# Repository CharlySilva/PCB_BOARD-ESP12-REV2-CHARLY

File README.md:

# PCB_BOARD-ESP12-REV2-CHARLY
# PCB in fabrication fase

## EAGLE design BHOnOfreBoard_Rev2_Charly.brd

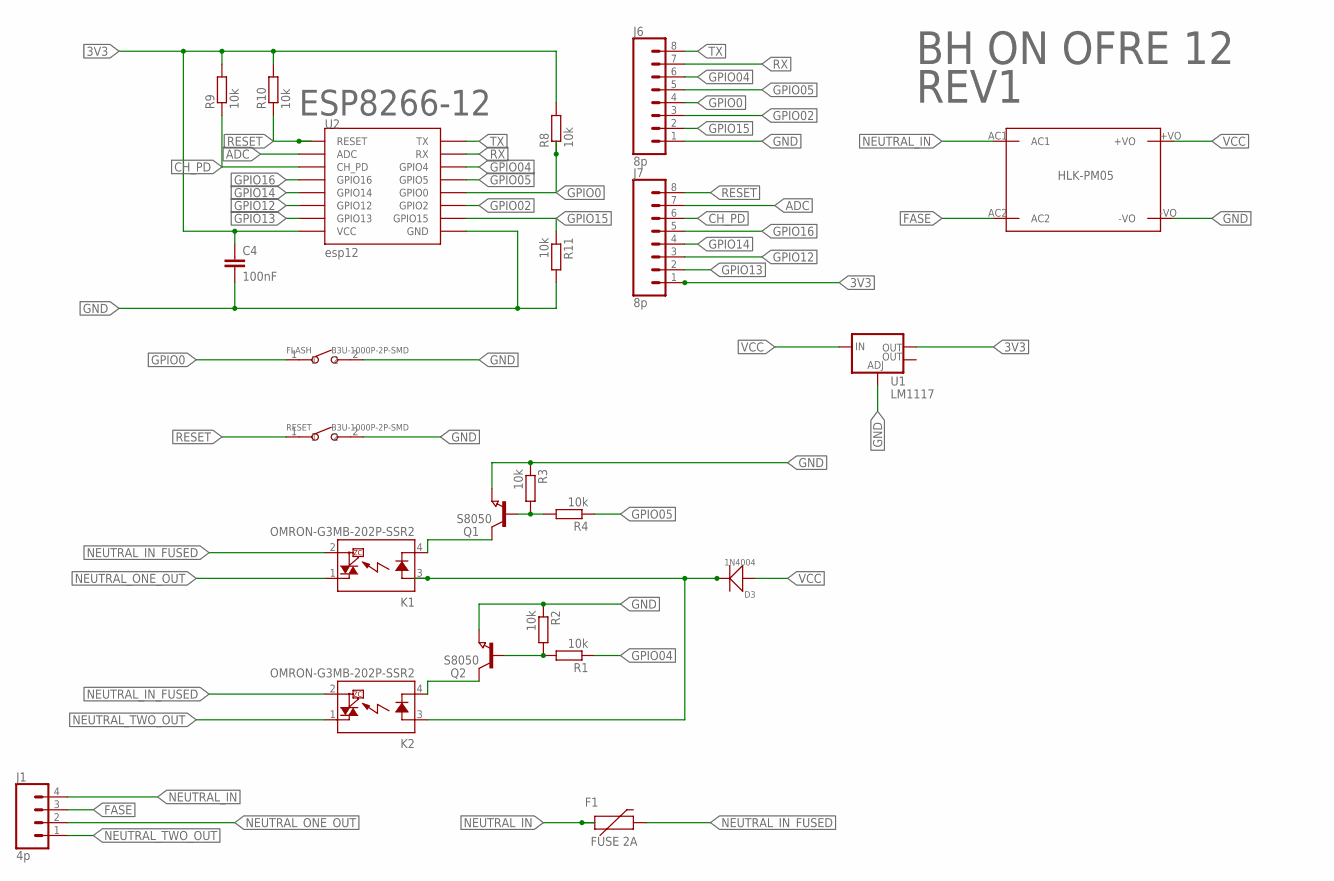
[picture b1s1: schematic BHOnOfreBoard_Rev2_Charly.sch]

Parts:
C4: 100nF; 0603
D3: 1N4004; DO-214AC
F1: FUSE 2A; PTH
FLASH: B3U-1000P-2P-SMD; SW2-2.6-3.0X2.5X1.2+0.4MM
J1: 4p; SCREWTERMINAL-3.5MM-4
J6, J7: 8p; 1X08
K1, K2: OMRON-G3MB-202P-SSR2; OMRON-G3MB-202P-SSR
Q1, Q2: S8050; SOT23
R1, R2, R3, R4, R8, R9, R10, R11: 10k; R0603
RESET: B3U-1000P-2P-SMD; SW2-2.6-3.0X2.5X1.2+0.4MM
U1: LM1117; SOT223
U2: esp12; ESP12-SMD
U$2: HLK-PM03

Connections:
3V3: C4.1, J7.1, R8.2, R9.2, R10.2, U1.2 (OUT), U2.VCC
ADC: J7.7, U2.ADC
CH_PD: J7.6, R9.1, U2.CH_PD
FASE: J1.3, U$2.AC2
GND: C4.2, FLASH.2, J6.1, Q1.2 (E), Q2.2 (E), R2.1, R3.1, R11.2, RESET.2, U1.1 (ADJ), U2.GND, U$2.-VO
GPIO0: FLASH.1, J6.4, R8.1, U2.GPIO0
GPIO02: J6.3, U2.GPIO2
GPIO04: J6.6, R1.1, U2.GPIO4
GPIO05: J6.5, R4.1, U2.GPIO5
GPIO12: J7.3, U2.GPIO12
GPIO13: J7.2, U2.GPIO13
GPIO14: J7.4, U2.GPIO14
GPIO15: J6.2, R11.1, U2.GPIO15
GPIO16: J7.5, U2.GPIO16
unnamed: K1.4 (K), Q1.3 (C)
unnamed: D3.2 (-), K1.3 (A), K2.3 (A)
unnamed: Q1.1 (B), R3.2, R4.2
unnamed: K2.4 (K), Q2.3 (C)
unnamed: Q2.1 (B), R1.2, R2.2
NEUTRAL_IN: F1.P$1 (1), J1.4, U$2.AC1
NEUTRAL_IN_FUSED: F1.P$2 (2), K1.2 (DS2), K2.2 (DS2)
NEUTRAL_ONE_OUT: J1.2, K1.1 (DS1)
NEUTRAL_TWO_OUT: J1.1, K2.1 (DS1)
RESET: J7.8, R10.1, RESET.1, U2.RESET
RX: J6.7, U2.RXD0 (RX)
TX: J6.8, U2.TXD0 (TX)
VCC: D3.1 (+), U1.3 (IN), U$2.+VO

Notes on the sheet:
HLK-PM05
BH ON OFRE 12
ESP8266-12
REV1

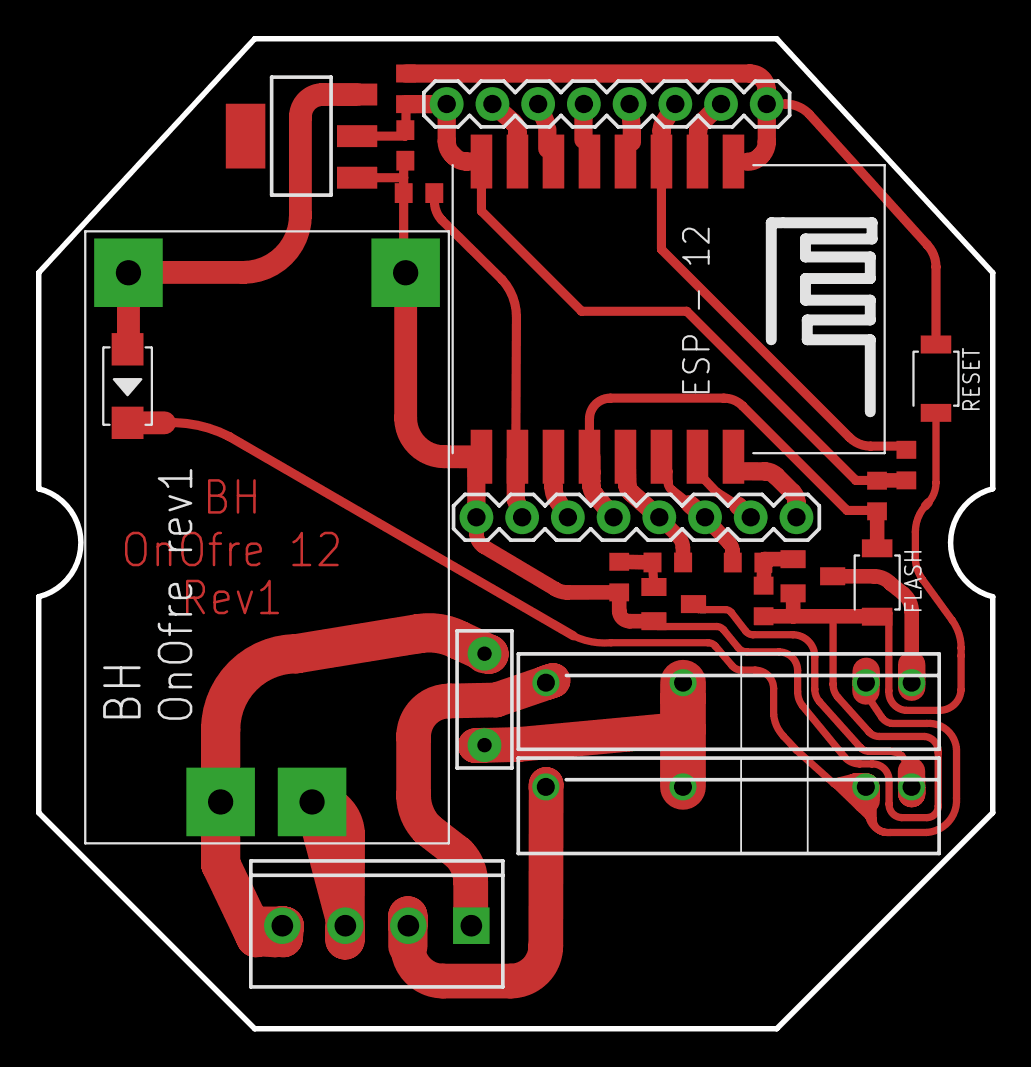
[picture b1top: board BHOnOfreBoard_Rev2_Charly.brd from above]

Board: 2 copper layers, 53.0 x 55.0 mm, 23 parts (0 on the bottom side), 27 nets.

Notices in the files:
parts and their libraries:
SparkFun-Connectors: Licensing: Creative Commons ShareAlike 4.0 International - https://creativecommons.org/licenses/by-sa/4.0
